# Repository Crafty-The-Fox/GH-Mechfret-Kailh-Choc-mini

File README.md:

# GH-Mechfret-Kailh-Choc-mini with LEDs!!!
Custom drop-in replacement for the fret PCB for Guitar Hero controllers using Kailh Choc Mini switches. Please check the license before use.

This should fit all guitars, I hope? You need a washer probably for some guitars.

LEDs are SK9822-ec20. You need to cut a bit of plastic off the switches case but its not completely horible and only takes 2 snips.

Side note: I actually havent ordered PCBs for this but i have test fitted it with a 3d printed one and it seems to work fine.

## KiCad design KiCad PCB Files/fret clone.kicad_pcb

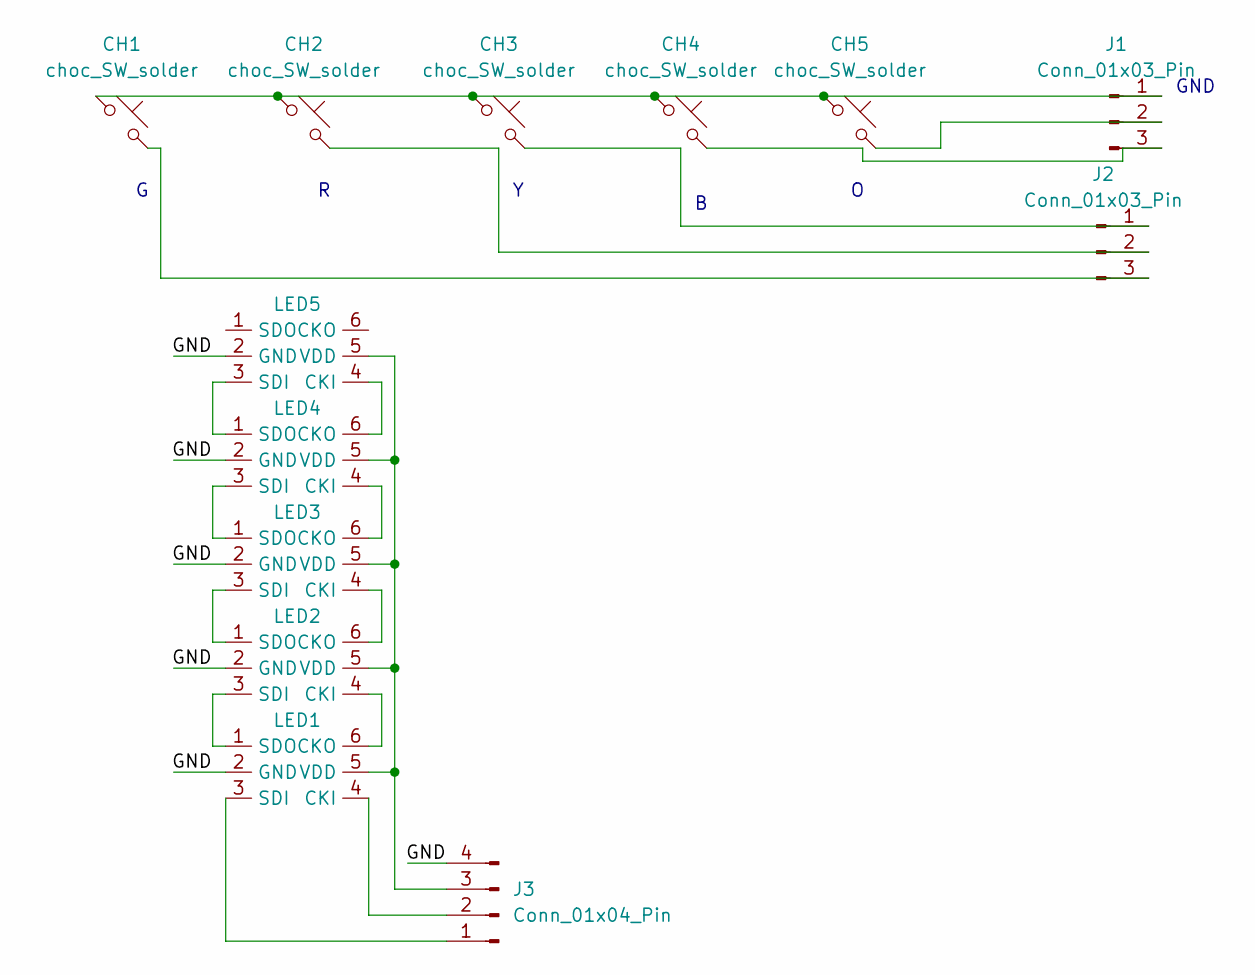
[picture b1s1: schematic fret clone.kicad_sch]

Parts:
CH1, CH2, CH3, CH4, CH5: choc_SW_solder; SW_Kailh_Choc_Mini
J1, J2: Conn_01x03_Pin; PinHeader_1x03_P2.54mm_Vertical
J3: Conn_01x04_Pin; PinHeader_1x04_P2.54mm_Vertical
LED1, LED2, LED3, LED4, LED5: SK9822-EC20

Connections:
/GND: J3.4, LED1.2 (GND), LED2.2 (GND), LED3.2 (GND), LED4.2 (GND), LED5.2 (GND)
unnamed: CH1.1, CH2.1, CH3.1, CH4.1, CH5.1, J1.1
unnamed: CH5.2, J1.2
unnamed: CH4.2, J1.3
unnamed: CH3.2, J2.1
unnamed: CH2.2, J2.2
unnamed: CH1.2, J2.3
unnamed: J3.1, LED1.3 (SDI)
unnamed: J3.2, LED1.4 (CKI)
unnamed: J3.3, LED1.5 (VDD), LED2.5 (VDD), LED3.5 (VDD), LED4.5 (VDD), LED5.5 (VDD)
unnamed: LED1.6 (CKO), LED2.4 (CKI)
unnamed: LED1.1 (SDO), LED2.3 (SDI)
unnamed: LED2.6 (CKO), LED3.4 (CKI)
unnamed: LED2.1 (SDO), LED3.3 (SDI)
unnamed: LED3.6 (CKO), LED4.4 (CKI)
unnamed: LED3.1 (SDO), LED4.3 (SDI)
unnamed: LED4.6 (CKO), LED5.4 (CKI)
unnamed: LED4.1 (SDO), LED5.3 (SDI)

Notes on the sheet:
GND

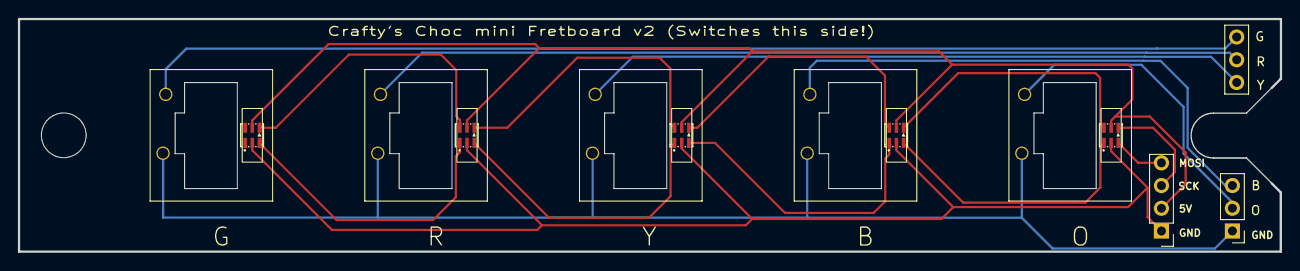
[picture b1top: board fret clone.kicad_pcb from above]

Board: 2 copper layers, 141.1 x 26.0 mm, 13 parts (0 on the bottom side), 18 nets.

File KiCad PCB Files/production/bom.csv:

Designator,Footprint,Quantity,Value,LCSC Part #
"CH1, CH2, CH3, CH4, CH5",SW_Kailh_Choc_Mini_1.00u,5,choc_SW_solder,
"J1, J2",PinHeader_1x03_P2.54mm_Vertical,2,Conn_01x03_Pin,

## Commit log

2023-11-21 Create LICENSE
2023-11-21 add kicad project
2024-01-09 add the things new LED
